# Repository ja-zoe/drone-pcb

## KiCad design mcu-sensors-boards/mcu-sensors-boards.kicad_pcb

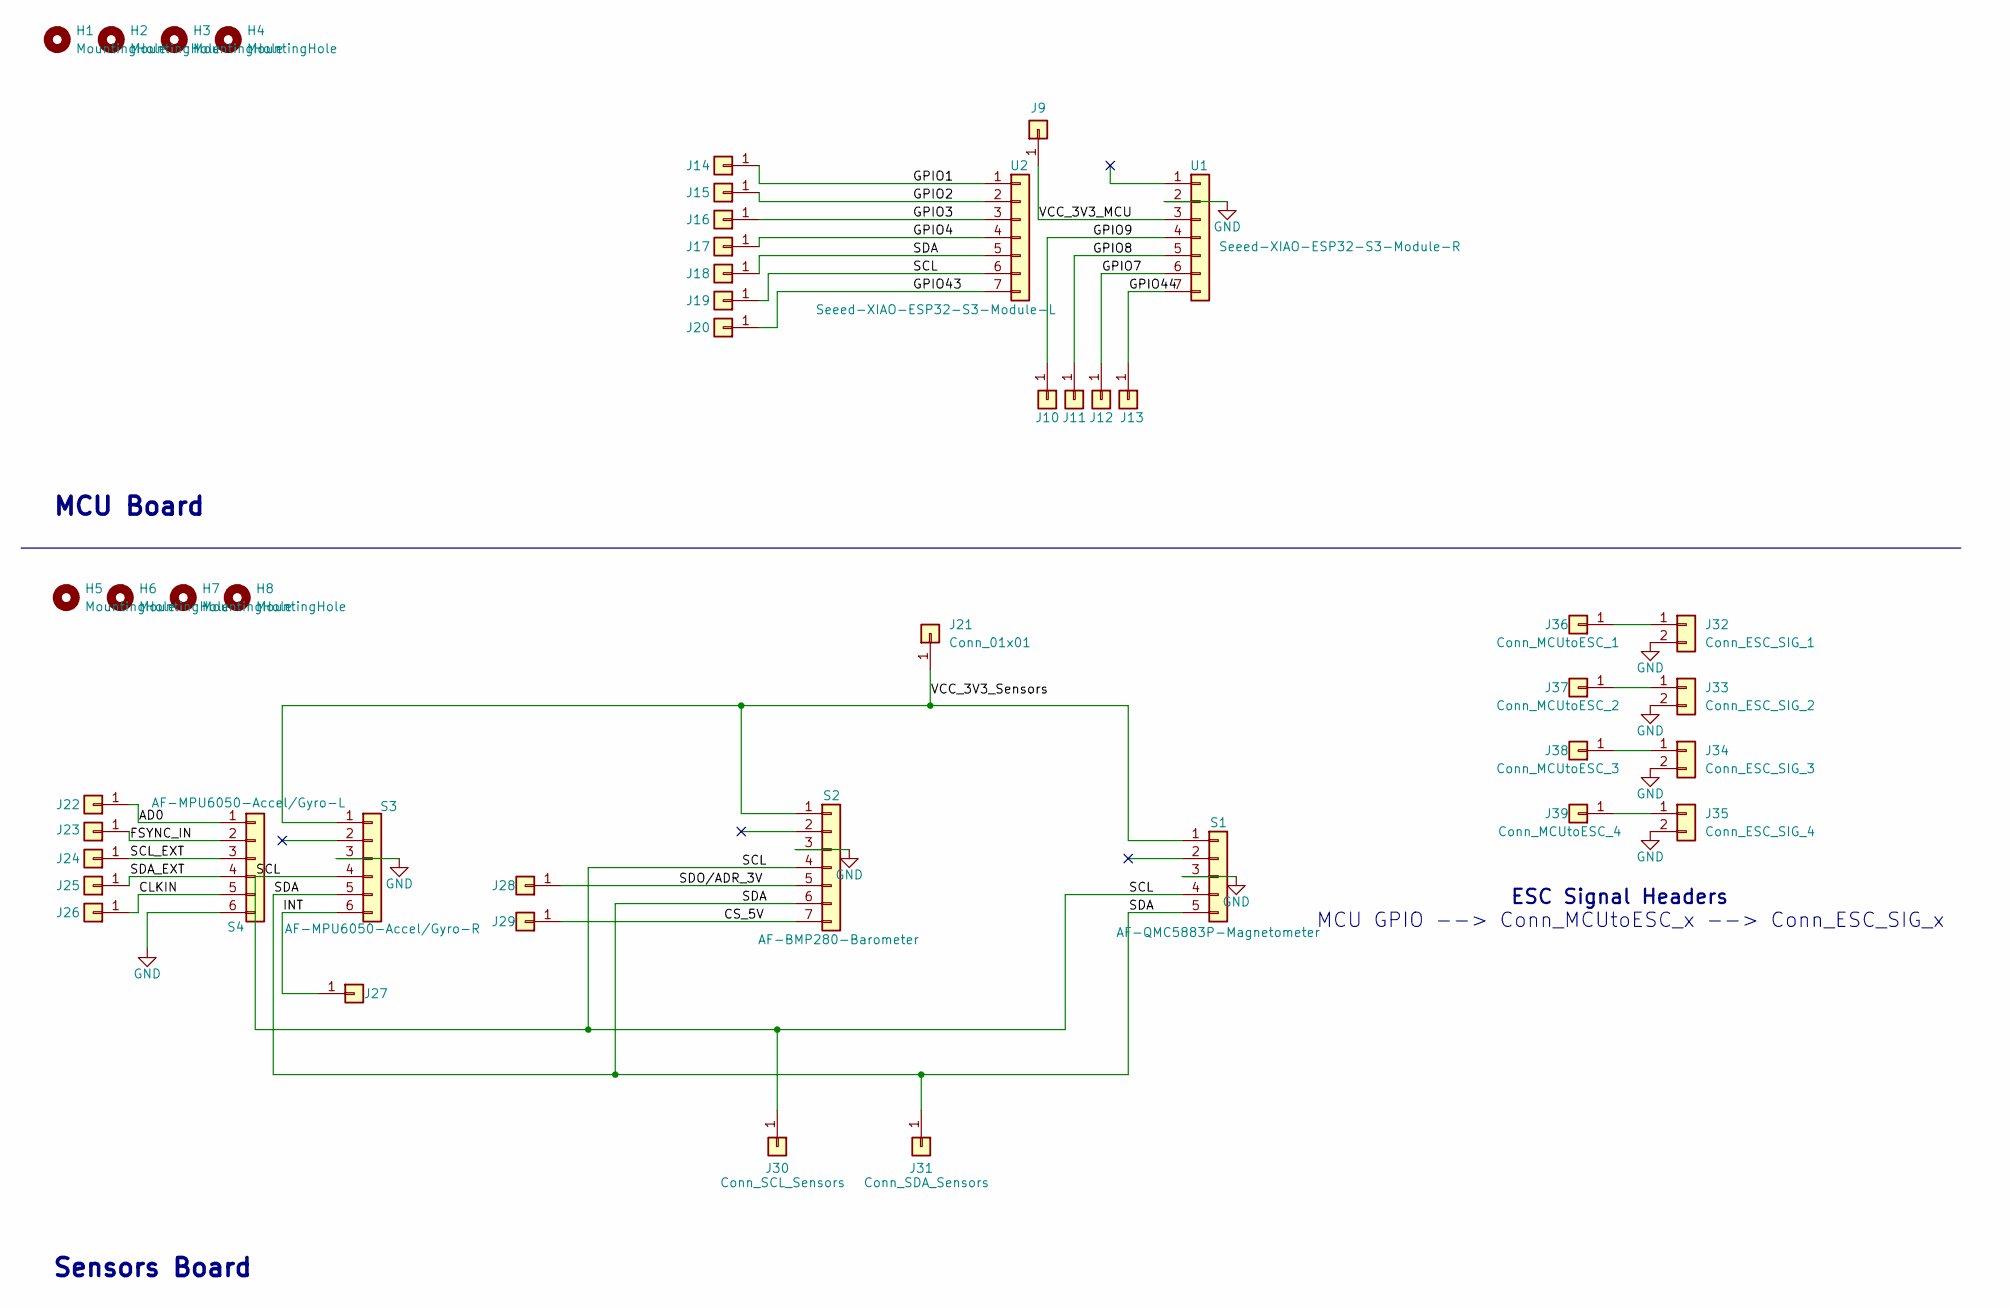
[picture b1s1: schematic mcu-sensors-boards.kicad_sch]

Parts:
H1, H2, H3, H4, H5, H6, H7, H8: MountingHole; MountingHole_3.2mm_M3_ISO14580_Pad_TopOnly
J9, J14, J15, J16, J17, J18, J19, J20, J21, J22, J23, J24, J25, J26, J27, J28, J29: Conn_01x01; SolderWire-0.1sqmm_1x01_D0.4mm_OD1mm
J10: GPIO9_TH; SolderWire-0.1sqmm_1x01_D0.4mm_OD1mm
J11: GPIO8 TH; SolderWire-0.1sqmm_1x01_D0.4mm_OD1mm
J12: GPIO7 TH; SolderWire-0.1sqmm_1x01_D0.4mm_OD1mm
J13: GPIO44 TH; SolderWire-0.1sqmm_1x01_D0.4mm_OD1mm
J30: Conn_SCL_Sensors; SolderWire-0.1sqmm_1x01_D0.4mm_OD1mm
J31: Conn_SDA_Sensors; SolderWire-0.1sqmm_1x01_D0.4mm_OD1mm
J32: Conn_ESC_SIG_1; SolderWire-0.1sqmm_1x02_P3.6mm_D0.4mm_OD1mm
J33: Conn_ESC_SIG_2; SolderWire-0.1sqmm_1x02_P3.6mm_D0.4mm_OD1mm
J34: Conn_ESC_SIG_3; SolderWire-0.1sqmm_1x02_P3.6mm_D0.4mm_OD1mm
J35: Conn_ESC_SIG_4; SolderWire-0.1sqmm_1x02_P3.6mm_D0.4mm_OD1mm
J36: Conn_MCUtoESC_1; SolderWire-0.1sqmm_1x01_D0.4mm_OD1mm
J37: Conn_MCUtoESC_2; SolderWire-0.1sqmm_1x01_D0.4mm_OD1mm
J38: Conn_MCUtoESC_3; SolderWire-0.1sqmm_1x01_D0.4mm_OD1mm
J39: Conn_MCUtoESC_4; SolderWire-0.1sqmm_1x01_D0.4mm_OD1mm
S1: AF-QMC5883P-Magnetometer; PinSocket_1x04_P2.54mm_Vertical
S2: AF-BMP280-Barometer; PinSocket_1x07_P2.54mm_Vertical
S3: AF-MPU6050-Accel/Gyro-R; PinSocket_1x06_P2.54mm_Vertical
S4: AF-MPU6050-Accel/Gyro-L; PinSocket_1x06_P2.54mm_Vertical
U1: Seeed-XIAO-ESP32-S3-Module-R; PinSocket_1x07_P2.54mm_Vertical
U2: Seeed-XIAO-ESP32-S3-Module-L; PinSocket_1x07_P2.54mm_Vertical

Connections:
/AD0: J22.1, S4.1
/CLKIN: J26.1, S4.5
/CS_5V: J29.1, S2.7
/FSYNC_IN: J23.1, S4.2
/GPIO1: J14.1, U2.1
/GPIO2: J15.1, U2.2
/GPIO3: J16.1, U2.3
/GPIO4: J17.1, U2.4
/GPIO7: J12.1, U1.6
/GPIO8: J11.1, U1.5
/GPIO9: J10.1, U1.4
/GPIO43: J20.1, U2.7
/GPIO44: J13.1, U1.7
/INT: J27.1, S3.6
/SCL: J19.1, J30.1, S1.4, S2.4, S3.4, U2.6
/SCL_EXT: J24.1, S4.3
/SDA: J18.1, J31.1, S1.5, S2.6, S3.5, U2.5
/SDA_EXT: J25.1, S4.4
/SDO/ADR_3V: J28.1, S2.5
/VCC_3V3_MCU: J9.1, U1.3
/VCC_3V3_Sensors: J21.1, S1.1, S2.1, S3.1
GND: J32.2, J33.2, J34.2, J35.2, S1.3, S2.3, S3.3, S4.6, U1.2
unnamed: J32.1, J36.1
unnamed: J33.1, J37.1
unnamed: J34.1, J38.1
unnamed: J35.1, J39.1

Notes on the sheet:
Sensors Board
MCU Board
ESC Signal Headers
MCU GPIO --> Conn_MCUtoESC_x --> Conn_ESC_SIG_x

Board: 2 copper layers, 45 parts (0 on the bottom side), 26 nets, no tracks yet.

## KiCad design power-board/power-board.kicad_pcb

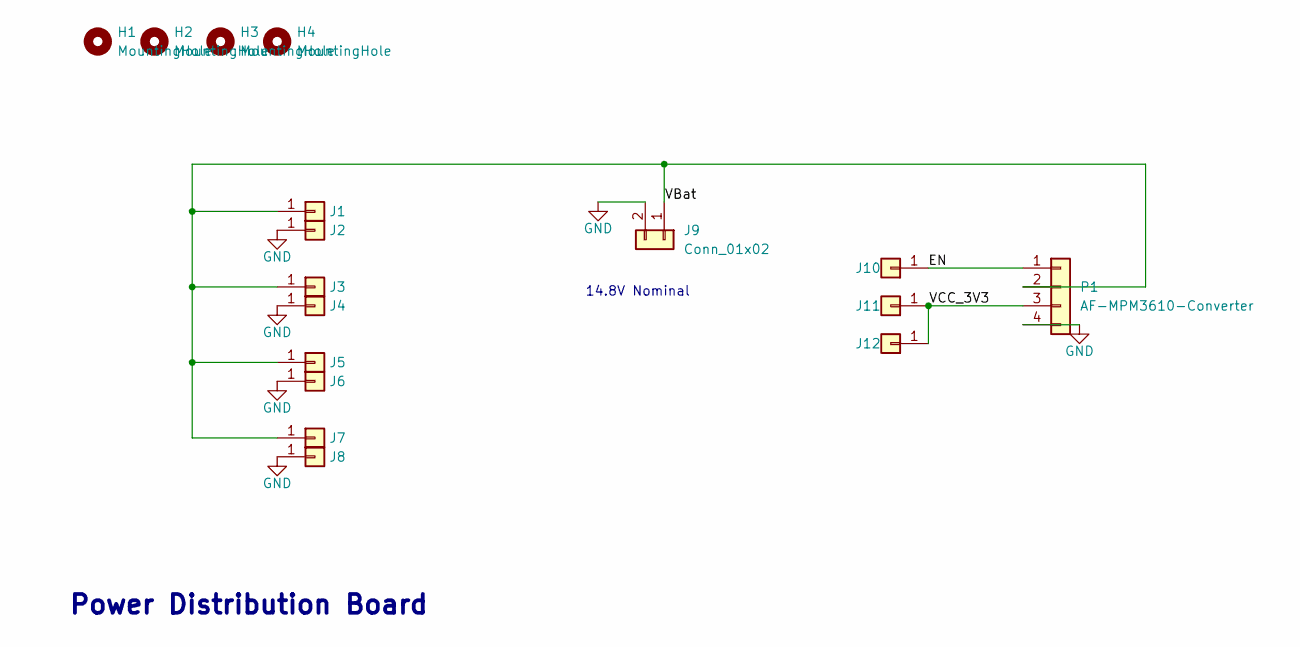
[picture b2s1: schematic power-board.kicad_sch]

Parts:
H1, H2, H3, H4: MountingHole; MountingHole_3.2mm_M3_ISO14580_Pad_TopOnly
J1: ESC_1_+; 01x01_ESC_Pad_Vias
J2: ESC_1_-; 01x01_ESC_Pad
J3: ESC_2_+; 01x01_ESC_Pad_Vias
J4: ESC_2_-; 01x01_ESC_Pad
J5: ESC_3_+; 01x01_ESC_Pad_Vias
J6: ESC_3_-; 01x01_ESC_Pad
J7: ESC_4_+; 01x01_ESC_Pad_Vias
J8: ESC_4_-; 01x01_ESC_Pad
J9: Conn_01x02; PDB_Battery_Pads_ViasL
J10, J11, J12: Conn_01x01; SolderWire-0.1sqmm_1x01_D0.4mm_OD1mm
P1: AF-MPM3610-Converter; PinSocket_1x04_P2.54mm_Vertical

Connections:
/EN: J10.1, P1.1
/VBat: J1.1, J1.2, J3.1, J3.2, J5.1, J5.2, J7.1, J7.2, J9.1, J9.3, P1.2
/VCC_3V3: J11.1, J12.1, P1.3
GND: J2.1, J4.1, J6.1, J8.1, J9.2, P1.4

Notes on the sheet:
14.8V Nominal
Power Distribution Board

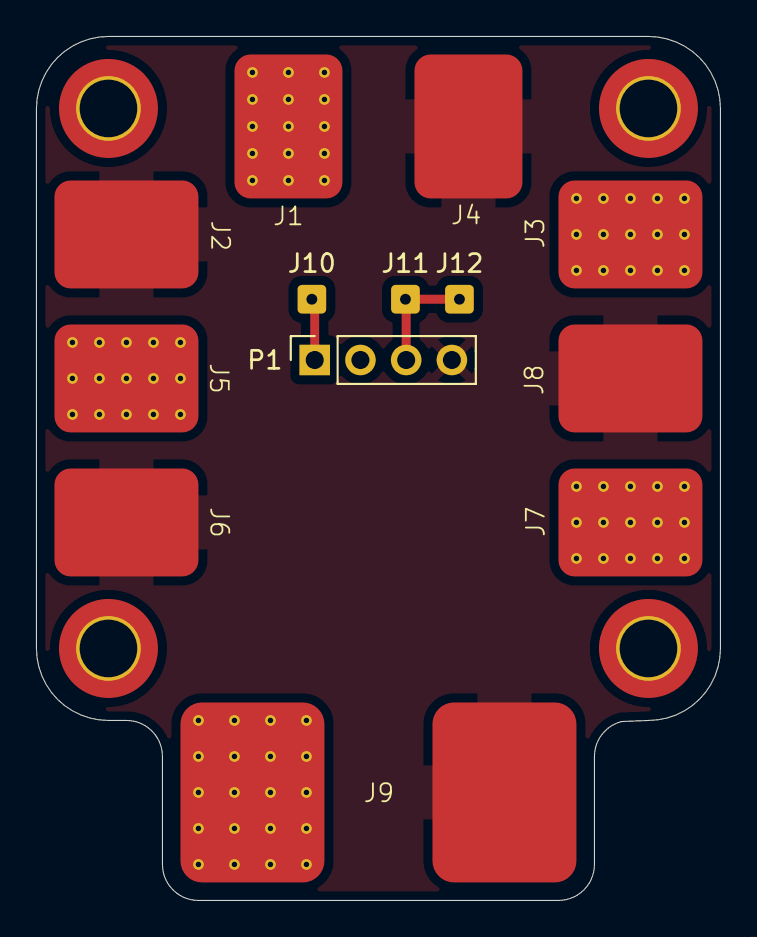
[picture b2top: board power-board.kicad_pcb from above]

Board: 2 copper layers, 38.0 x 48.0 mm, 17 parts (0 on the bottom side), 4 nets.

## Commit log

2025-08-27 Added sensors and mcu
2025-09-19 Initial commit 2
2025-10-02 separate main schematic from power-board
